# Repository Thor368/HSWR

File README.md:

# HSWR
Fork of the original VESC V6 to support up to 200V and 100A (depending on cooling)

#Work in progress (see http://vedder.se/forums/viewtopic.php?f=16&t=568)

#Gen1
Alpha Prototype on self etched boards. Never worked properly.

#Gen2
Four layer design in industry production quality. First working prototype.

#Gen3
Thicker copper layers for higher current capability. Had issues with current sampling.

#Gen3.1
Never was a board but a mod of Gen3. First prototype with Hall current sensors. Worked very well but needed a proper board.

#Gen4
- changed current sensors to halleffect sensors
- many changes in the IO (including connectors breaking backwards compatibility)
- HSWR can now interface with Tritium motor interface boards
- IO now fully isolated from HV
- fan drive
- changed MOSFET mounting mechanism for higher clamping force and reliablity
- some minimal mechanical changes breaking backwards compatibility to HSWR3 housing

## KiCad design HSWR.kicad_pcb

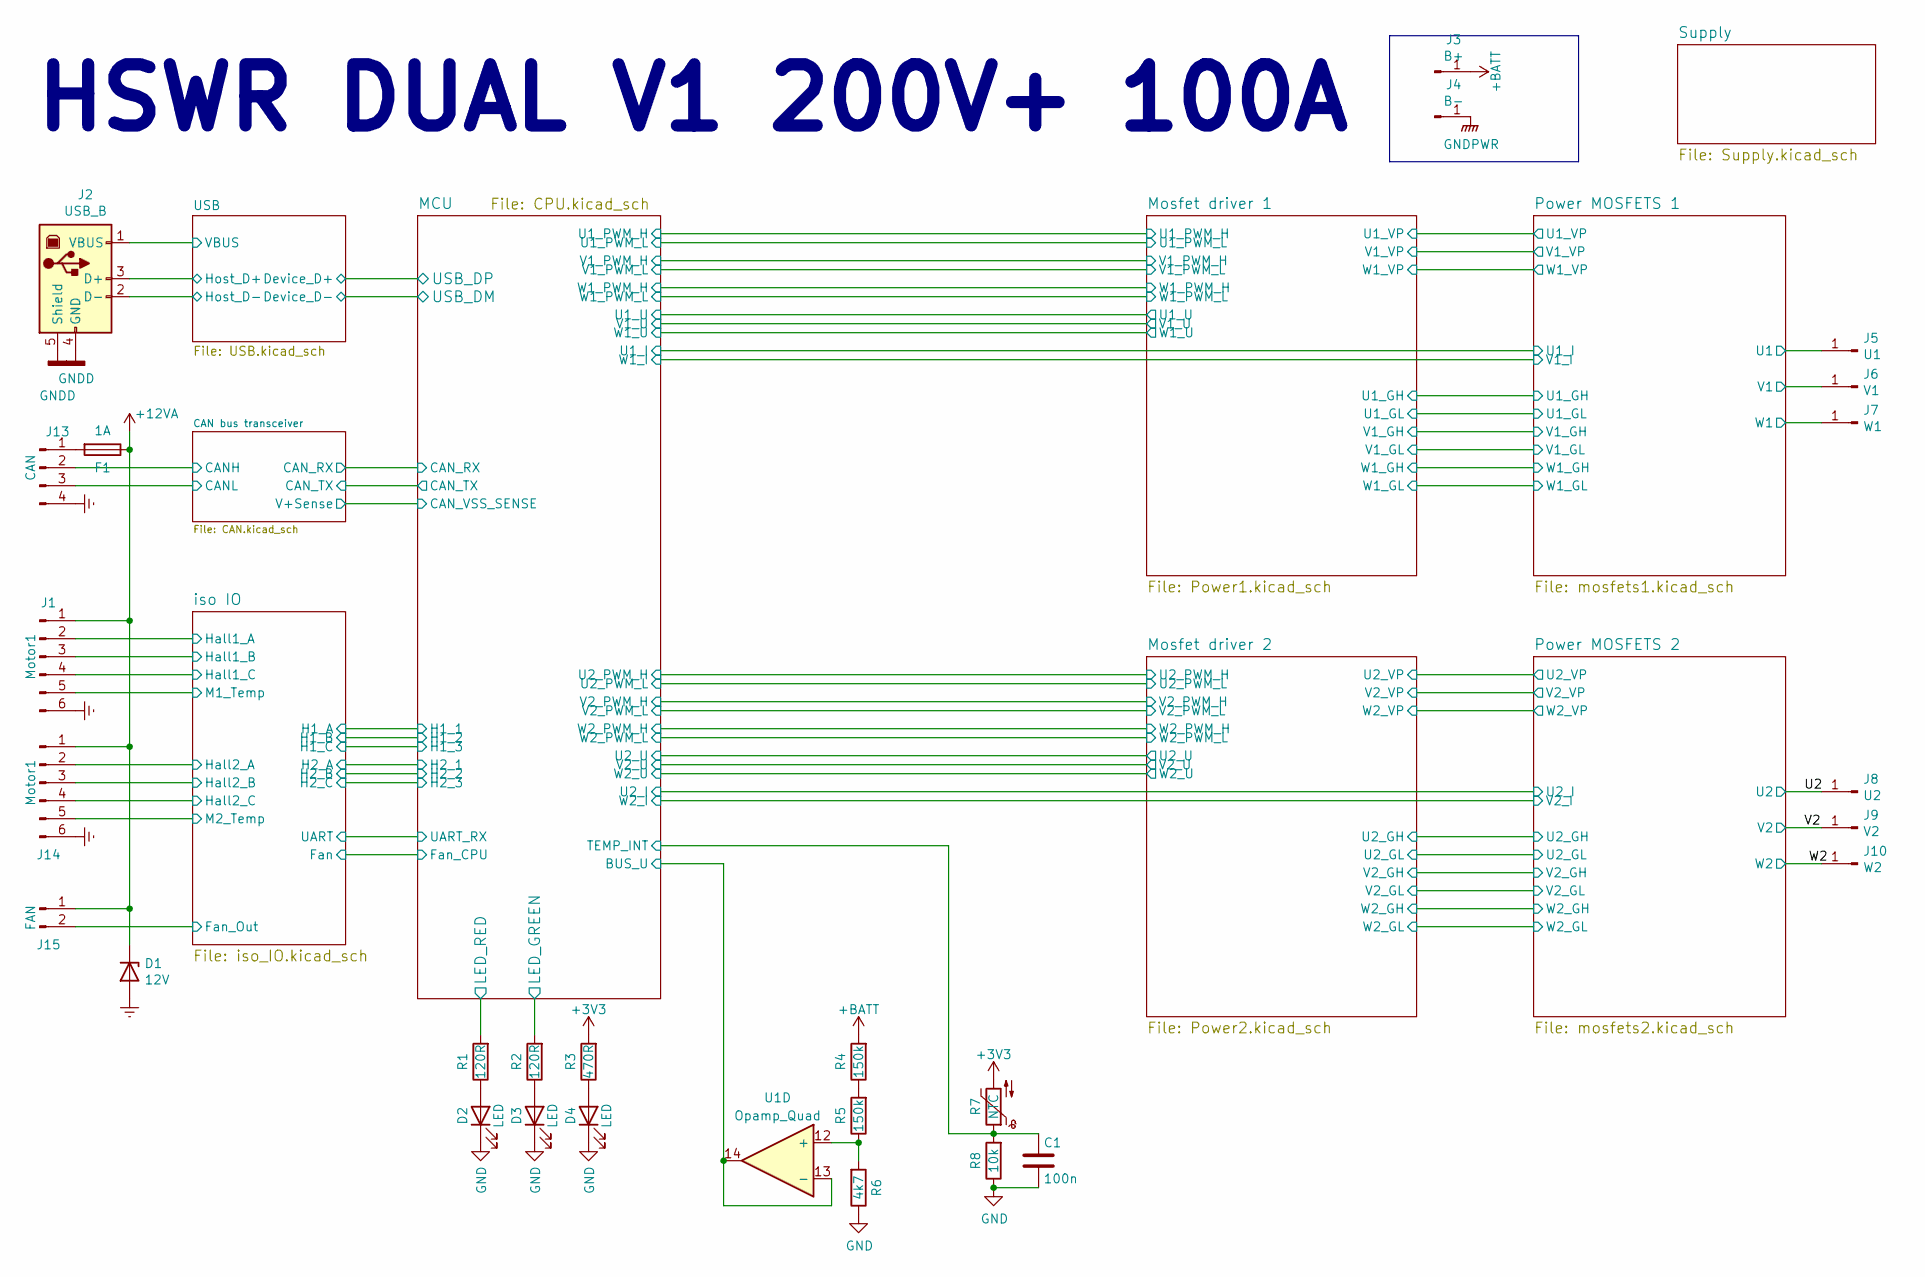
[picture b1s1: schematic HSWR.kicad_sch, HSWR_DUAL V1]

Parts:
C1: 100n; C_0805_2012Metric
D1: 12V; D_SMA
D2, D3, D4: LED; LED_0805_2012Metric
F1: 1A; Fuse_Littelfuse-NANO2-451_453
J1, J14: Motor1; PhoenixContact_MCV_1,5_6-G-3.5_1x06_P3.50mm_Vertical
J2: USB_B; USB_B_TE_5787834_Vertical
J3: B+; MountingHole_6.5mm_Pad_Via
J4: B-; MountingHole_6.5mm_Pad_Via
J5: U1; MountingHole_6.5mm_Pad_Via
J6: V1; MountingHole_6.5mm_Pad_Via
J7: W1; MountingHole_6.5mm_Pad_Via
J8: U2; MountingHole_6.5mm_Pad_Via
J9: V2; MountingHole_6.5mm_Pad_Via
J10: W2; MountingHole_6.5mm_Pad_Via
J13: CAN; PhoenixContact_MCV_1,5_4-G-3.5_1x04_P3.50mm_Vertical
J15: FAN; PhoenixContact_MCV_1,5_2-G-3.5_1x02_P3.50mm_Vertical
R1, R2: 120R; R_0805_2012Metric
R3: 470R; R_0805_2012Metric
R4, R5: 150k; R_0805_2012Metric
R6: 4k7; R_0805_2012Metric
R7: NTC; R_0603_1608Metric
R8: 10k; R_0805_2012Metric
U1: Opamp_Quad; SO-14_3.9x8.65mm_P1.27mm

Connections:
+3V3: R3.2, R7.2; also elsewhere on the board
+12VA: D1.1 (K), F1.1, J1.1, J14.1, J15.1; also elsewhere on the board
+BATT: J3.1, R4.2; also elsewhere on the board
/CAN bus transceiver/CANH: J13.2; also elsewhere on the board
/CAN bus transceiver/CANL: J13.3; also elsewhere on the board
/MCU/BUS_U: U1.13 (-), U1.14; also elsewhere on the board
/MCU/LED_GREEN: R2.2; also elsewhere on the board
/MCU/LED_RED: R1.2; also elsewhere on the board
/MCU/TEMP_INT: C1.1, R7.1, R8.2; also elsewhere on the board
/Mosfet driver 1/W1_VP: J7.1; also elsewhere on the board
/Power MOSFETS 1/U1: J5.1; also elsewhere on the board
/Power MOSFETS 1/V1: J6.1; also elsewhere on the board
/U2: J8.1; also elsewhere on the board
/USB/Host_D+: J2.3 (D+); also elsewhere on the board
/USB/Host_D-: J2.2 (D-); also elsewhere on the board
/USB/VBUS: J2.1 (VBUS); also elsewhere on the board
/V2: J9.1; also elsewhere on the board
/W2: J10.1; also elsewhere on the board
/iso IO/Fan_Out: J15.2; also elsewhere on the board
/iso IO/Hall1_A: J1.2; also elsewhere on the board
/iso IO/Hall1_B: J1.3; also elsewhere on the board
/iso IO/Hall1_C: J1.4; also elsewhere on the board
/iso IO/Hall2_A: J14.2; also elsewhere on the board
/iso IO/Hall2_B: J14.3; also elsewhere on the board
/iso IO/Hall2_C: J14.4; also elsewhere on the board
/iso IO/M1_Temp: J1.5; also elsewhere on the board
/iso IO/M2_Temp: J14.5; also elsewhere on the board
Earth: D1.2 (A), J1.6, J13.4, J14.6; also elsewhere on the board
GND: C1.2, D2.1 (K), D3.1 (K), D4.1 (K), R6.1, R8.1; also elsewhere on the board
GNDD: J2.4 (GND), J2.5 (Shield); also elsewhere on the board
GNDPWR: J4.1; also elsewhere on the board
unnamed: D2.2 (A), R1.1
unnamed: D3.2 (A), R2.1
unnamed: D4.2 (A), R3.1
unnamed: F1.2, J13.1
unnamed: R4.1, R5.2
unnamed: R5.1, R6.2, U1.12 (+)

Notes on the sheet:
HSWR DUAL V1 200V+ 100A

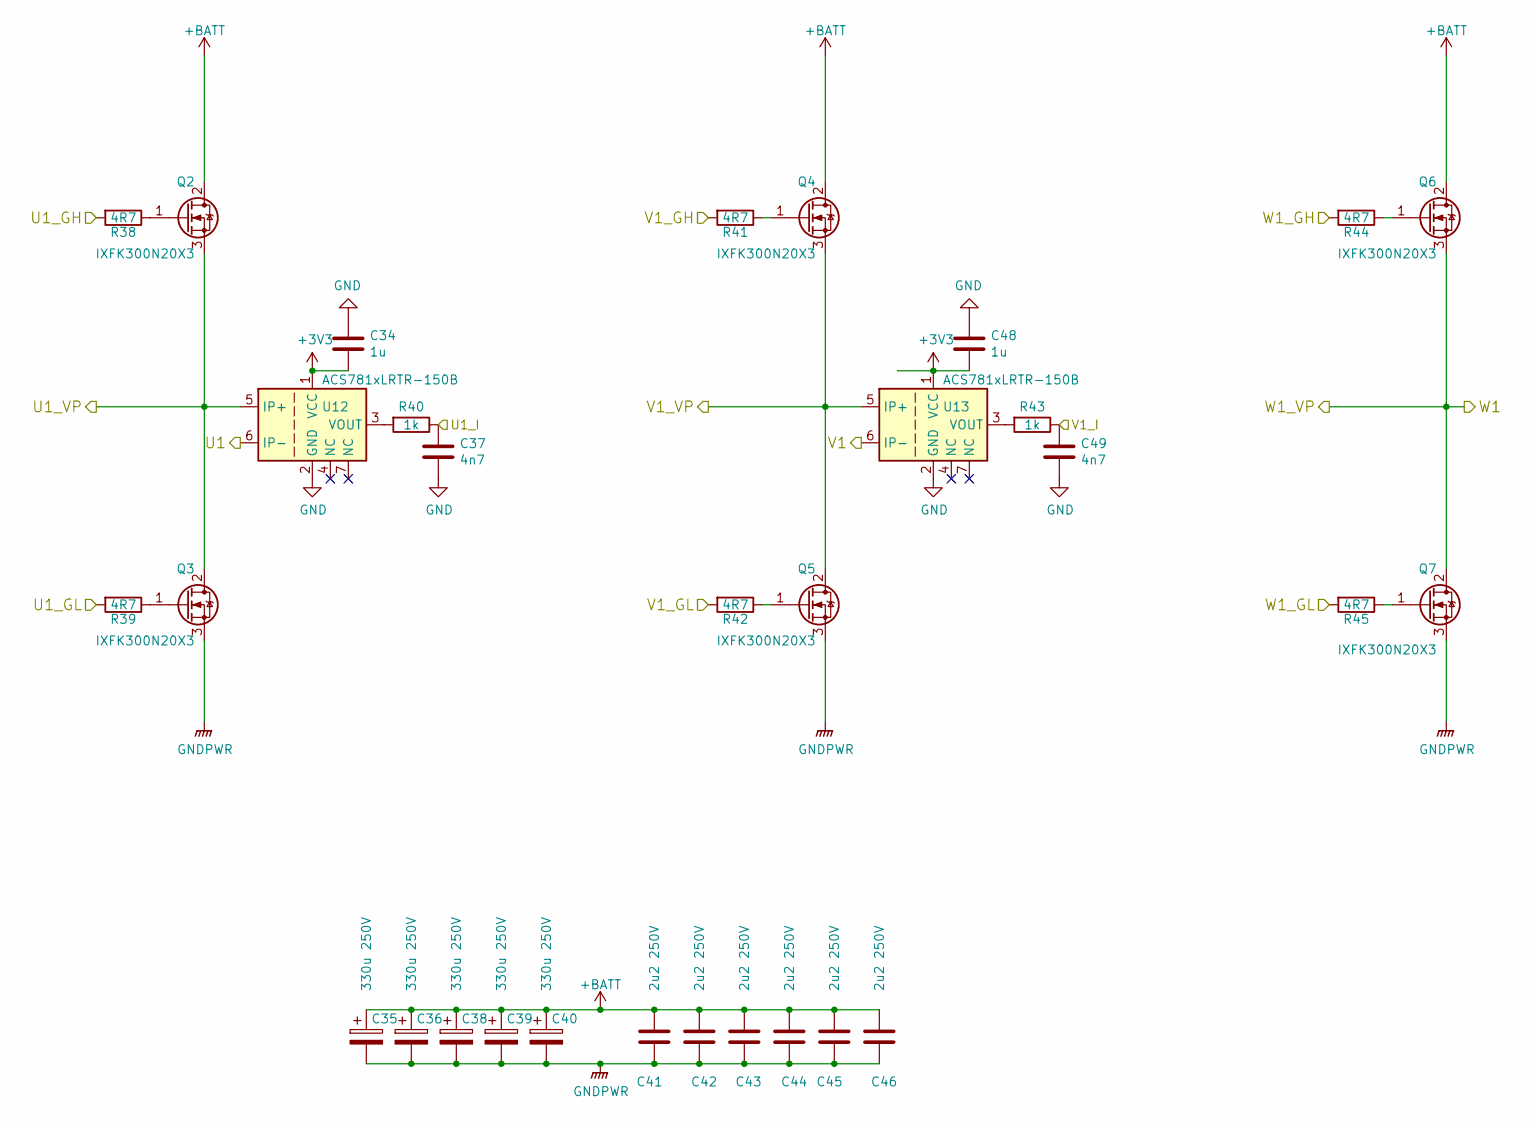
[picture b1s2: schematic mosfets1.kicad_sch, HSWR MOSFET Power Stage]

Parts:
C34, C48: 1u; C_0805_2012Metric
C35, C36, C38, C39, C40: 330u 250V; CP_Radial_D22.0mm_P10.00mm_SnapIn
C37, C49: 4n7; C_0805_2012Metric
C41, C42, C43, C44, C45, C46: 2u2 250V; C_2220_5750Metric
Q2, Q3, Q4, Q5, Q6, Q7: IXFK300N20X3; TO-264-3_Horizontal_TabUp_6mm_hole
R38, R39, R41, R42, R44, R45: 4R7; R_0805_2012Metric
R40, R43: 1k; R_0805_2012Metric
U12, U13: ACS781xLRTR-150B; Allegro_PSOF-7_4.8x6.4mm_P1.60mm

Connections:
+3V3: C34.2, C48.2, U12.1 (VCC), U13.1 (VCC); also elsewhere on the board
+BATT: C35.1, C36.1, C38.1, C39.1, C40.1, C41.1, C42.1, C43.1, C44.1, C45.1, C46.1, Q2.2 (D), Q4.2 (D), Q6.2 (D); also elsewhere on the board
/MCU/U1_I: C37.1, R40.1; also elsewhere on the board
/MCU/W1_I: C49.1, R43.1; also elsewhere on the board
/Mosfet driver 1/U1_GH: R38.2; also elsewhere on the board
/Mosfet driver 1/U1_GL: R39.2; also elsewhere on the board
/Mosfet driver 1/U1_VP: Q2.3 (S), Q3.2 (D), U12.5 (IP+); also elsewhere on the board
/Mosfet driver 1/V1_GH: R41.2; also elsewhere on the board
/Mosfet driver 1/V1_GL: R42.2; also elsewhere on the board
/Mosfet driver 1/V1_VP: Q4.3 (S), Q5.2 (D), U13.5 (IP+); also elsewhere on the board
/Mosfet driver 1/W1_GH: R44.2; also elsewhere on the board
/Mosfet driver 1/W1_GL: R45.2; also elsewhere on the board
/Mosfet driver 1/W1_VP: Q6.3 (S), Q7.2 (D); also elsewhere on the board
/Power MOSFETS 1/U1: U12.6 (IP-); also elsewhere on the board
/Power MOSFETS 1/V1: U13.6 (IP-); also elsewhere on the board
GND: C34.1, C37.2, C48.1, C49.2, U12.2 (GND), U13.2 (GND); also elsewhere on the board
GNDPWR: C35.2, C36.2, C38.2, C39.2, C40.2, C41.2, C42.2, C43.2, C44.2, C45.2, C46.2, Q3.3 (S), Q5.3 (S), Q7.3 (S); also elsewhere on the board
unnamed: Q2.1 (G), R38.1
unnamed: Q3.1 (G), R39.1
unnamed: Q4.1 (G), R41.1
unnamed: Q5.1 (G), R42.1
unnamed: Q6.1 (G), R44.1
unnamed: Q7.1 (G), R45.1
unnamed: R40.2, U12.3 (VOUT)
unnamed: R43.2, U13.3 (VOUT)

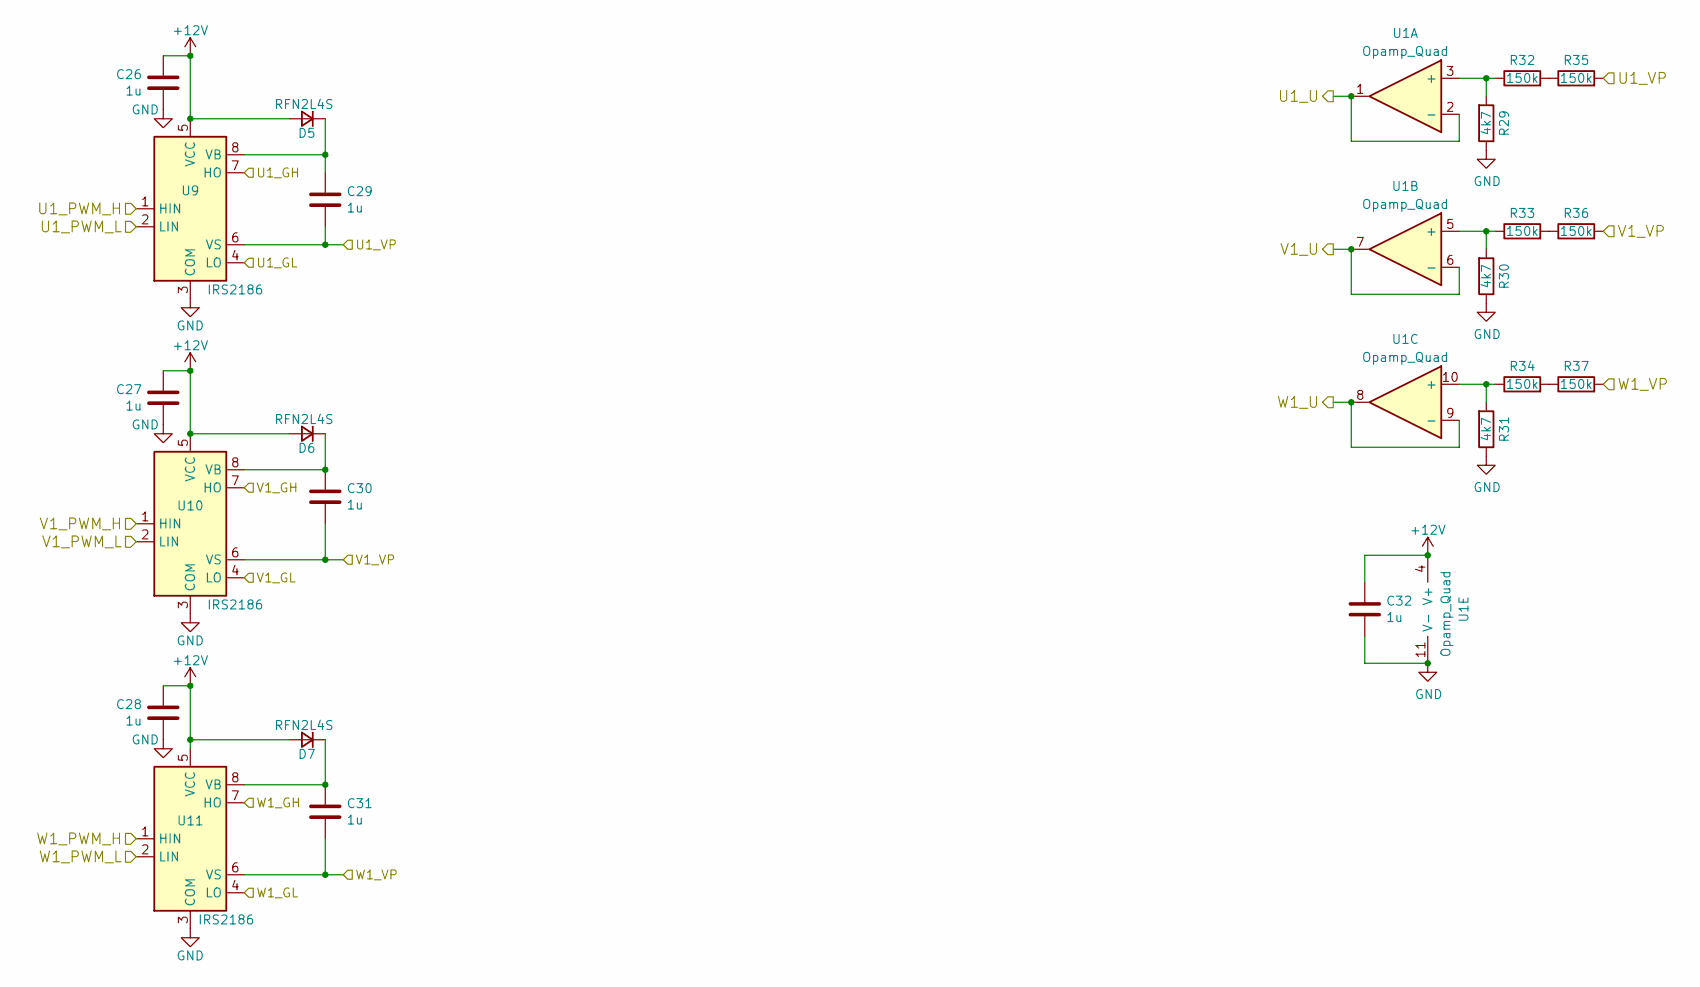
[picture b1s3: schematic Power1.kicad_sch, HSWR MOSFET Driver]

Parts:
C26, C27, C28, C29, C30, C31, C32: 1u; C_0805_2012Metric
D5, D6, D7: RFN2L4S; D_SOD-123
R29, R30, R31: 4k7; R_0805_2012Metric
R32, R33, R34, R35, R36, R37: 150k; R_0805_2012Metric
U1: Opamp_Quad; SO-14_3.9x8.65mm_P1.27mm
U9, U10, U11: IRS2186; SOIC-8_3.9x4.9mm_P1.27mm

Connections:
+12V: C26.2, C27.2, C28.2, C32.1, D5.2 (A), D6.2 (A), D7.2 (A), U1.4 (V+), U9.5 (VCC), U10.5 (VCC), U11.5 (VCC); also elsewhere on the board
/MCU/U1_PWM_H: U9.1 (HIN); also elsewhere on the board
/MCU/U1_PWM_L: U9.2 (LIN); also elsewhere on the board
/MCU/U1_U: U1.1, U1.2 (-); also elsewhere on the board
/MCU/V1_PWM_H: U10.1 (HIN); also elsewhere on the board
/MCU/V1_PWM_L: U10.2 (LIN); also elsewhere on the board
/MCU/V1_U: U1.6 (-), U1.7; also elsewhere on the board
/MCU/W1_PWM_H: U11.1 (HIN); also elsewhere on the board
/MCU/W1_PWM_L: U11.2 (LIN); also elsewhere on the board
/MCU/W1_U: U1.8, U1.9 (-); also elsewhere on the board
/Mosfet driver 1/U1_GH: U9.7 (HO); also elsewhere on the board
/Mosfet driver 1/U1_GL: U9.4 (LO); also elsewhere on the board
/Mosfet driver 1/U1_VP: C29.2, R35.2, U9.6 (VS); also elsewhere on the board
/Mosfet driver 1/V1_GH: U10.7 (HO); also elsewhere on the board
/Mosfet driver 1/V1_GL: U10.4 (LO); also elsewhere on the board
/Mosfet driver 1/V1_VP: C30.2, R36.2, U10.6 (VS); also elsewhere on the board
/Mosfet driver 1/W1_GH: U11.7 (HO); also elsewhere on the board
/Mosfet driver 1/W1_GL: U11.4 (LO); also elsewhere on the board
/Mosfet driver 1/W1_VP: C31.2, R37.2, U11.6 (VS); also elsewhere on the board
GND: C26.1, C27.1, C28.1, C32.2, R29.1, R30.1, R31.1, U1.11 (V-), U9.3 (COM), U10.3 (COM), U11.3 (COM); also elsewhere on the board
unnamed: C29.1, D5.1 (K), U9.8 (VB)
unnamed: C30.1, D6.1 (K), U10.8 (VB)
unnamed: C31.1, D7.1 (K), U11.8 (VB)
unnamed: R32.2, R35.1
unnamed: R33.2, R36.1
unnamed: R34.2, R37.1
unnamed: R29.2, R32.1, U1.3 (+)
unnamed: R30.2, R33.1, U1.5 (+)
unnamed: R31.2, R34.1, U1.10 (+)

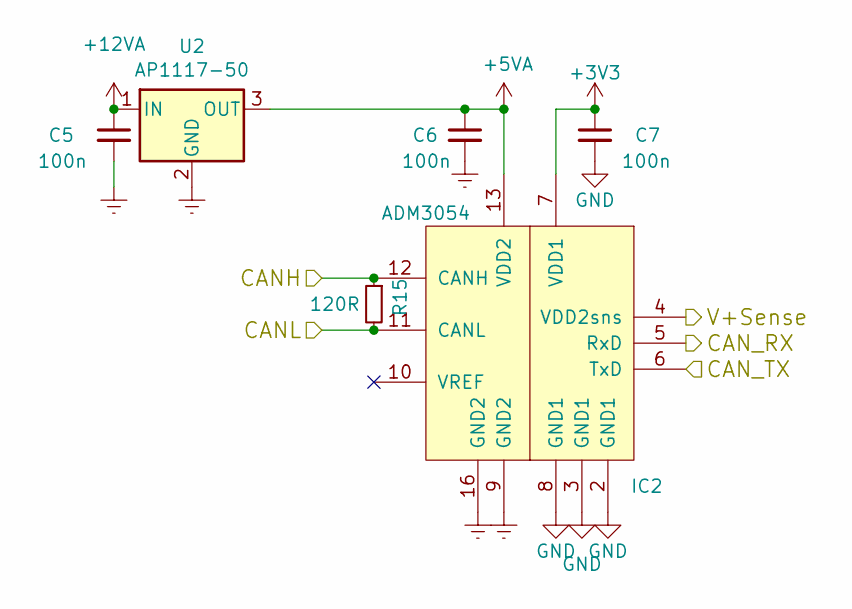
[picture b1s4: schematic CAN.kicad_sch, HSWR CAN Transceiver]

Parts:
C5, C6, C7: 100n; C_0805_2012Metric
IC2: ADM3054; SOIC-16W_7.5x10.3mm_P1.27mm
R15: 120R; R_0805_2012Metric
U2: AP1117-50; SOT-223-3_TabPin2

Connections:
+3V3: C7.1, IC2.7 (VDD1); also elsewhere on the board
+5VA: C6.1, IC2.13 (VDD2), U2.3 (OUT); also elsewhere on the board
+12VA: C5.1, U2.1 (IN); also elsewhere on the board
/CAN bus transceiver/CANH: IC2.12 (CANH), R15.1; also elsewhere on the board
/CAN bus transceiver/CANL: IC2.11 (CANL), R15.2; also elsewhere on the board
/CAN bus transceiver/CAN_RX: IC2.5 (RxD); also elsewhere on the board
/CAN bus transceiver/CAN_TX: IC2.6 (TxD); also elsewhere on the board
/CAN bus transceiver/V+Sense: IC2.4 (VDD2sns); also elsewhere on the board
Earth: C5.2, C6.2, IC2.9 (GND2), IC2.16 (GND2), U2.2 (GND); also elsewhere on the board
GND: C7.2, IC2.2 (GND1), IC2.3 (GND1), IC2.8 (GND1); also elsewhere on the board

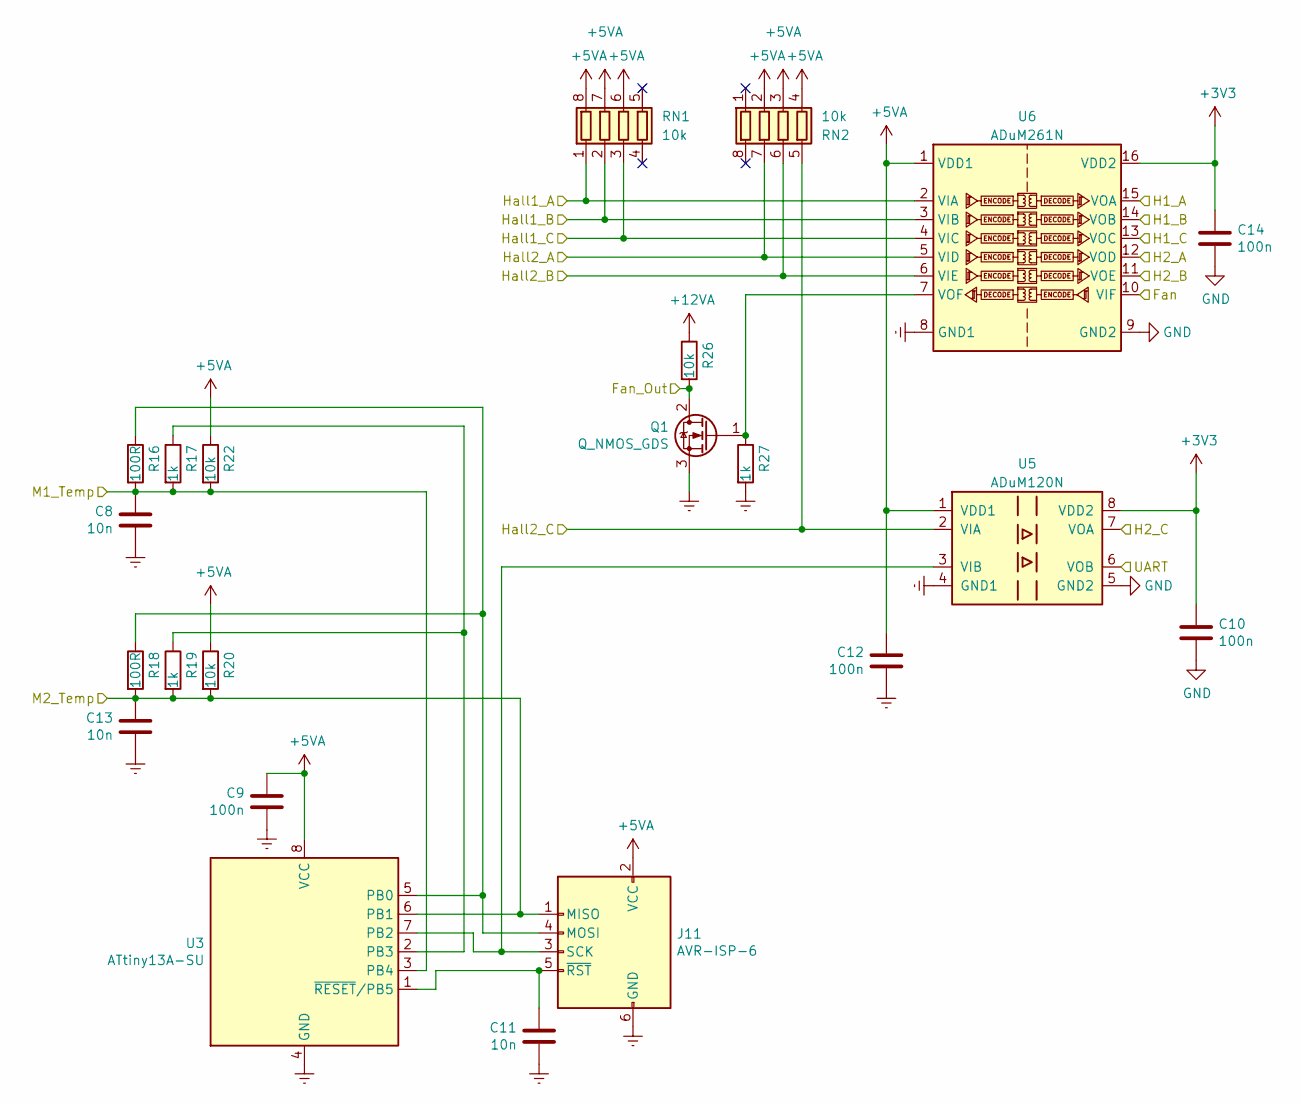
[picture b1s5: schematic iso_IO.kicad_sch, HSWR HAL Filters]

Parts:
C8, C11, C13: 10n; C_0805_2012Metric
C9, C10, C12, C14: 100n; C_0805_2012Metric
J11: AVR-ISP-6; PinHeader_2x03_P2.54mm_Vertical
Q1: Q_NMOS_GDS; SOT-223-3_TabPin2
R16, R18: 100R; R_0805_2012Metric
R17, R19, R27: 1k; R_0805_2012Metric
R20, R22, R26: 10k; R_0805_2012Metric
RN1, RN2: 10k; R_Array_Convex_4x0603
U3: ATtiny13A-SU; SO-8_5.3x6.2mm_P1.27mm
U5: ADuM120N; SOIC-8_3.9x4.9mm_P1.27mm
U6: ADuM261N; SOIC-16W_7.5x12.8mm_P1.27mm

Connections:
+3V3: C10.1, C14.1, U5.8 (VDD2), U6.16 (VDD2); also elsewhere on the board
+5VA: C9.1, C12.1, J11.2 (VCC), R20.1, R22.1, RN1.6 (R3.2), RN1.7 (R2.2), RN1.8 (R1.2), RN2.2 (R2.1), RN2.3 (R3.1), RN2.4 (R4.1), U3.8 (VCC), U5.1 (VDD1), U6.1 (VDD1); also elsewhere on the board
+12VA: R26.1; also elsewhere on the board
/MCU/Fan_CPU: U6.10 (VIF); also elsewhere on the board
/MCU/H1_1: U6.15 (VOA); also elsewhere on the board
/MCU/H1_2: U6.14 (VOB); also elsewhere on the board
/MCU/H1_3: U6.13 (VOC); also elsewhere on the board
/MCU/H2_1: U6.12 (VOD); also elsewhere on the board
/MCU/H2_2: U6.11 (VOE); also elsewhere on the board
/MCU/H2_3: U5.7 (VOA); also elsewhere on the board
/MCU/UART_RX: U5.6 (VOB); also elsewhere on the board
/iso IO/Fan_Out: Q1.2 (D), R26.2; also elsewhere on the board
/iso IO/Hall1_A: RN1.1 (R1.1), U6.2 (VIA); also elsewhere on the board
/iso IO/Hall1_B: RN1.2 (R2.1), U6.3 (VIB); also elsewhere on the board
/iso IO/Hall1_C: RN1.3 (R3.1), U6.4 (VIC); also elsewhere on the board
/iso IO/Hall2_A: RN2.7 (R2.2), U6.5 (VID); also elsewhere on the board
/iso IO/Hall2_B: RN2.6 (R3.2), U6.6 (VIE); also elsewhere on the board
/iso IO/Hall2_C: RN2.5 (R4.2), U5.2 (VIA); also elsewhere on the board
/iso IO/M1_Temp: C8.1, R16.2, R17.2, R22.2, U3.3 (PB4); also elsewhere on the board
/iso IO/M2_Temp: C13.1, J11.1 (MISO), R18.2, R19.2, R20.2, U3.6 (PB1); also elsewhere on the board
Earth: C8.2, C9.2, C11.2, C12.2, C13.2, J11.6 (GND), Q1.3 (S), R27.2, U3.4 (GND), U5.4 (GND1), U6.8 (GND1); also elsewhere on the board
GND: C10.2, C14.2, U5.5 (GND2), U6.9 (GND2); also elsewhere on the board
unnamed: J11.4 (MOSI), R16.1, R18.1, U3.5 (PB0)
unnamed: J11.3 (SCK), U3.7 (PB2), U5.3 (VIB)
unnamed: C11.1, J11.5 (~RST), U3.1 (~RESET/PB5)
unnamed: Q1.1 (G), R27.1, U6.7 (VOF)
unnamed: R17.1, R19.1, U3.2 (PB3)

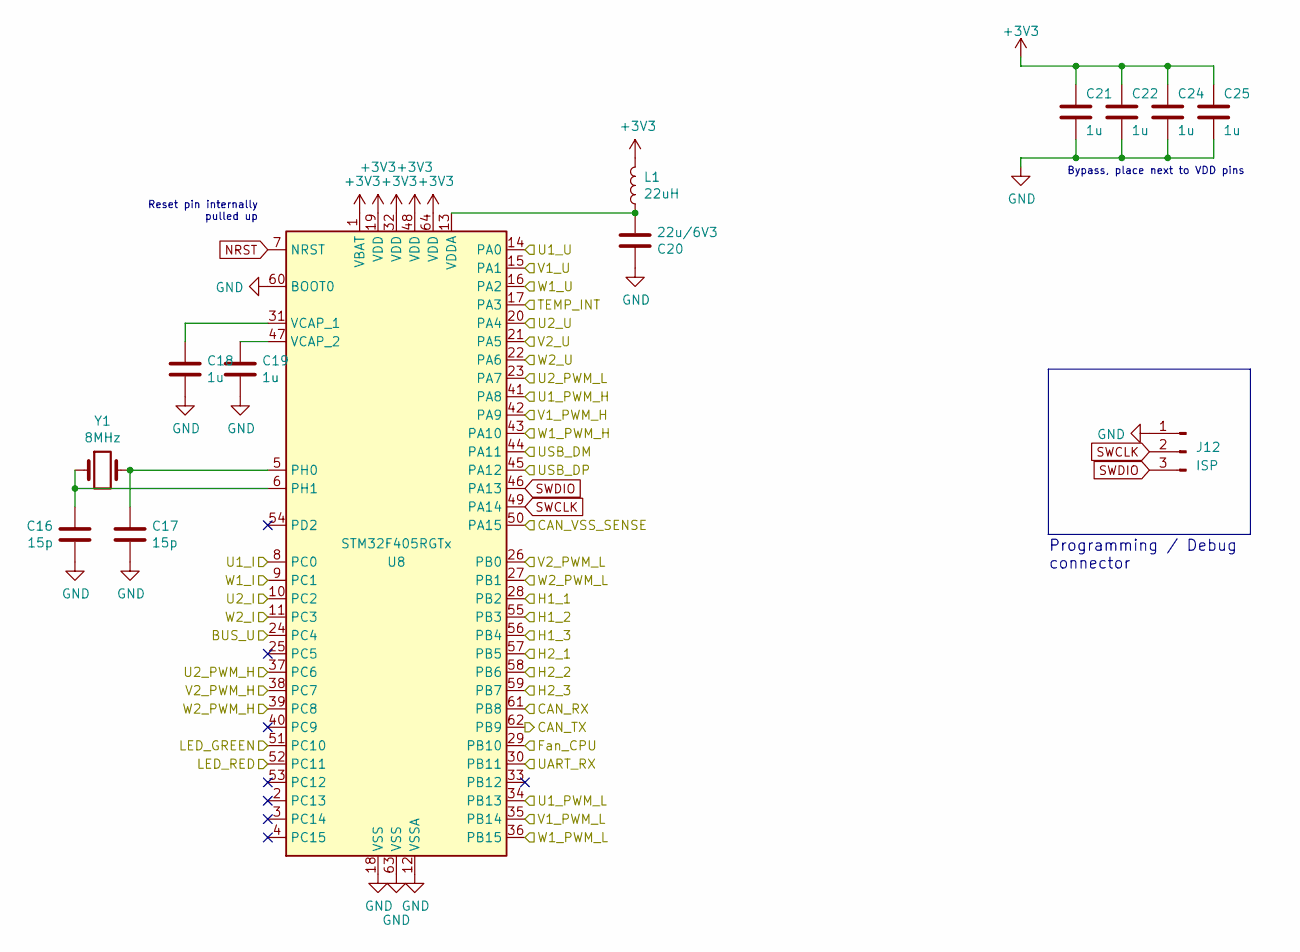
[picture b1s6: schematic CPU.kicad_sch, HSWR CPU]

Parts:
C16, C17: 15p; C_0805_2012Metric
C18, C19, C21, C22, C24, C25: 1u; C_0805_2012Metric
C20: 22u/6V3; C_0805_2012Metric
J12: ISP; PinHeader_1x03_P2.54mm_Vertical
L1: 22uH; L_0805_2012Metric
U8: STM32F405RGTx; LQFP-64_10x10mm_P0.5mm
Y1: 8MHz; Crystal_HC49-4H_Vertical

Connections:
+3V3: C21.1, C22.1, C24.1, C25.1, L1.2, U8.1 (VBAT), U8.19 (VDD), U8.32 (VDD), U8.48 (VDD), U8.64 (VDD); also elsewhere on the board
/CAN bus transceiver/CAN_RX: U8.61 (PB8); also elsewhere on the board
/CAN bus transceiver/CAN_TX: U8.62 (PB9); also elsewhere on the board
/CAN bus transceiver/V+Sense: U8.50 (PA15); also elsewhere on the board
/MCU/BUS_U: U8.24 (PC4); also elsewhere on the board
/MCU/Fan_CPU: U8.29 (PB10); also elsewhere on the board
/MCU/H1_1: U8.28 (PB2); also elsewhere on the board
/MCU/H1_2: U8.55 (PB3); also elsewhere on the board
/MCU/H1_3: U8.56 (PB4); also elsewhere on the board
/MCU/H2_1: U8.57 (PB5); also elsewhere on the board
/MCU/H2_2: U8.58 (PB6); also elsewhere on the board
/MCU/H2_3: U8.59 (PB7); also elsewhere on the board
/MCU/LED_GREEN: U8.51 (PC10); also elsewhere on the board
/MCU/LED_RED: U8.52 (PC11); also elsewhere on the board
/MCU/TEMP_INT: U8.17 (PA3); also elsewhere on the board
/MCU/U1_I: U8.8 (PC0); also elsewhere on the board
/MCU/U1_PWM_H: U8.41 (PA8); also elsewhere on the board
/MCU/U1_PWM_L: U8.34 (PB13); also elsewhere on the board
/MCU/U1_U: U8.14 (PA0); also elsewhere on the board
/MCU/U2_I: U8.10 (PC2); also elsewhere on the board
/MCU/U2_PWM_H: U8.37 (PC6); also elsewhere on the board
/MCU/U2_PWM_L: U8.23 (PA7); also elsewhere on the board
/MCU/U2_U: U8.20 (PA4); also elsewhere on the board
/MCU/UART_RX: U8.30 (PB11); also elsewhere on the board
/MCU/USB_DM: U8.44 (PA11); also elsewhere on the board
/MCU/USB_DP: U8.45 (PA12); also elsewhere on the board
/MCU/V1_PWM_H: U8.42 (PA9); also elsewhere on the board
/MCU/V1_PWM_L: U8.35 (PB14); also elsewhere on the board
/MCU/V1_U: U8.15 (PA1); also elsewhere on the board
/MCU/V2_PWM_H: U8.38 (PC7); also elsewhere on the board
/MCU/V2_PWM_L: U8.26 (PB0); also elsewhere on the board
/MCU/V2_U: U8.21 (PA5); also elsewhere on the board
/MCU/W1_I: U8.9 (PC1); also elsewhere on the board
/MCU/W1_PWM_H: U8.43 (PA10); also elsewhere on the board
/MCU/W1_PWM_L: U8.36 (PB15); also elsewhere on the board
/MCU/W1_U: U8.16 (PA2); also elsewhere on the board
/MCU/W2_I: U8.11 (PC3); also elsewhere on the board
/MCU/W2_PWM_H: U8.39 (PC8); also elsewhere on the board
/MCU/W2_PWM_L: U8.27 (PB1); also elsewhere on the board
/MCU/W2_U: U8.22 (PA6); also elsewhere on the board
GND: C16.1, C17.2, C18.2, C19.2, C20.1, C21.2, C22.2, C24.2, C25.2, J12.1, U8.12 (VSSA), U8.18 (VSS), U8.60 (BOOT0), U8.63 (VSS); also elsewhere on the board
NRST: U8.7 (NRST)
unnamed: C17.1, U8.5 (PH0), Y1.2
unnamed: C16.2, U8.6 (PH1), Y1.1
unnamed: C18.1, U8.31 (VCAP_1)
unnamed: C19.1, U8.47 (VCAP_2)
unnamed: C20.2, L1.1, U8.13 (VDDA)
SWCLK: J12.2, U8.49 (PA14)
SWDIO: J12.3, U8.46 (PA13)

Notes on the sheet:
Reset pin internally pulled up
Bypass, place next to VDD pins
Programming / Debug connector

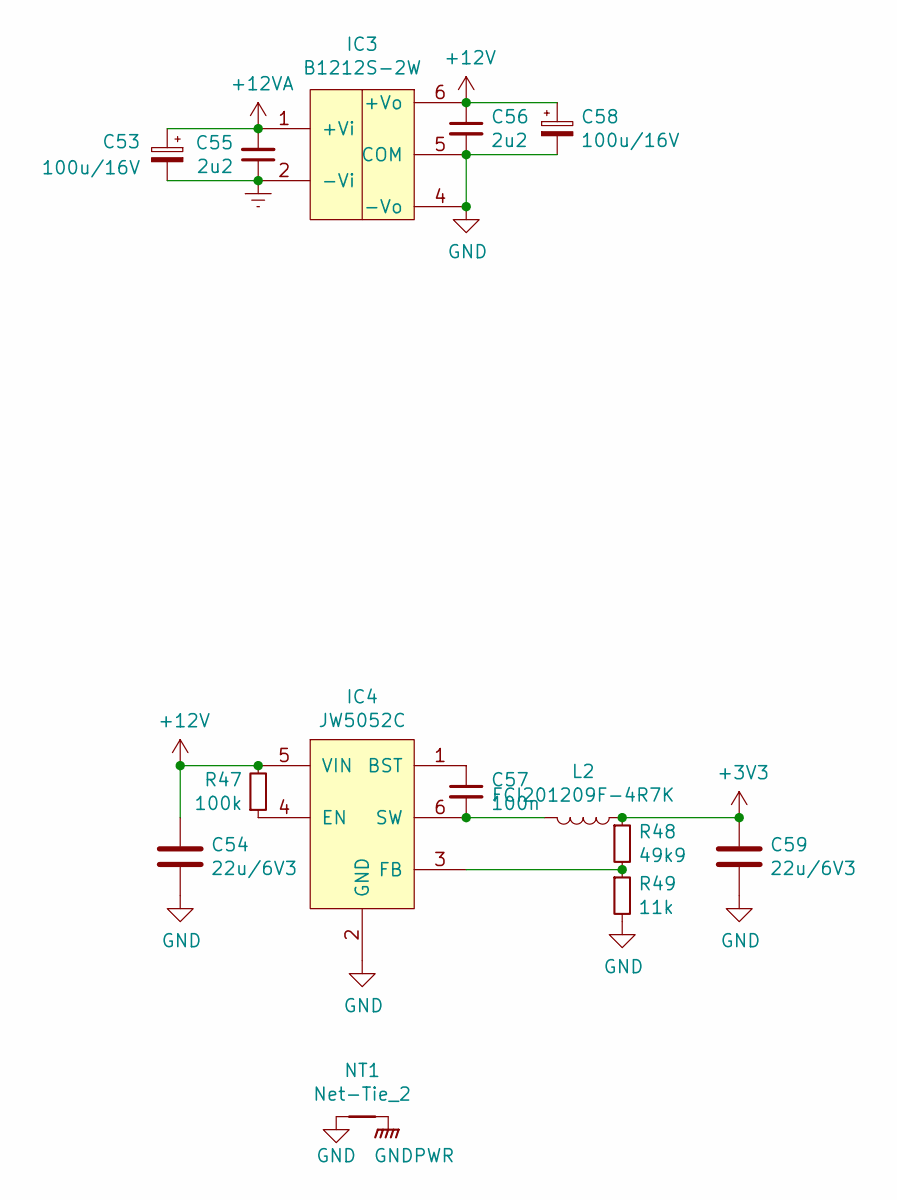
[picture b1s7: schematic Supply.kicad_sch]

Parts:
C53, C58: 100u/16V; CP_Radial_D6.3mm_P2.50mm
C54, C59: 22u/6V3; C_0805_2012Metric
C55, C56: 2u2; C_0805_2012Metric
C57: 100n; C_0805_2012Metric
IC3: B1212S-2W; Converter_DCDC_muRata_NMAxxxxSC_THT
IC4: JW5052C; TSOT-23-6
L2: FCI201209F-4R7K; L_0805_2012Metric
NT1: Net-Tie_2; NetTie-2_SMD_Pad2.0mm
R47: 100k; R_0805_2012Metric
R48: 49k9; R_0805_2012Metric
R49: 11k; R_0805_2012Metric

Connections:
+3V3: C59.1, L2.1, R48.1; also elsewhere on the board
+12V: C54.1, C56.1, C58.1, IC3.6 (+Vo), IC4.5 (VIN), R47.2; also elsewhere on the board
+12VA: C53.1, C55.2, IC3.1 (+Vi); also elsewhere on the board
Earth: C53.2, C55.1, IC3.2 (-Vi); also elsewhere on the board
GND: C54.2, C56.2, C58.2, C59.2, IC3.4 (-Vo), IC3.5 (COM), IC4.2 (GND), NT1.1, R49.2; also elsewhere on the board
GNDPWR: NT1.2; also elsewhere on the board
unnamed: C57.1, IC4.1 (BST)
unnamed: IC4.4 (EN), R47.1
unnamed: IC4.3 (FB), R48.2, R49.1
unnamed: C57.2, IC4.6 (SW), L2.2

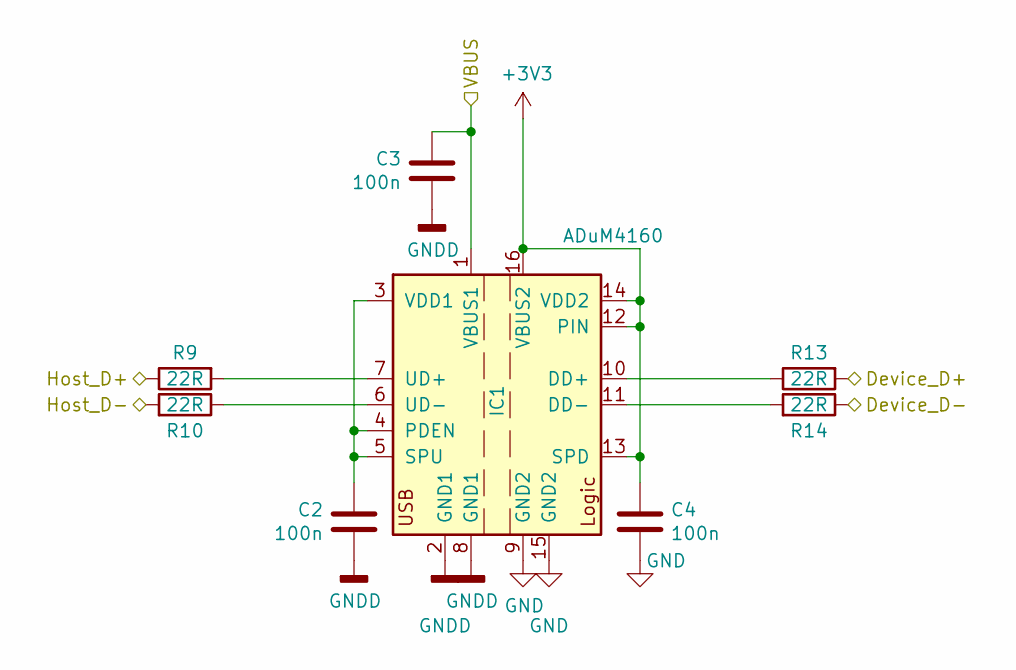
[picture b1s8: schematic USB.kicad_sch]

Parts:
C2, C3, C4: 100n; C_0805_2012Metric
IC1: ADuM4160; SOIC-16W_7.5x10.3mm_P1.27mm
R9, R10, R13, R14: 22R; R_0805_2012Metric

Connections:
+3V3: C4.2, IC1.12 (PIN), IC1.13 (SPD), IC1.14 (VDD2), IC1.16 (VBUS2); also elsewhere on the board
/MCU/USB_DM: R14.1; also elsewhere on the board
/MCU/USB_DP: R13.2; also elsewhere on the board
/USB/Host_D+: R9.1; also elsewhere on the board
/USB/Host_D-: R10.2; also elsewhere on the board
/USB/VBUS: C3.2, IC1.1 (VBUS1); also elsewhere on the board
GND: C4.1, IC1.9 (GND2), IC1.15 (GND2); also elsewhere on the board
GNDD: C2.1, C3.1, IC1.2 (GND1), IC1.8 (GND1); also elsewhere on the board
unnamed: IC1.10 (DD+), R13.1
unnamed: IC1.11 (DD-), R14.2
unnamed: C2.2, IC1.3 (VDD1), IC1.4 (PDEN), IC1.5 (SPU)
unnamed: IC1.7 (UD+), R9.2
unnamed: IC1.6 (UD-), R10.1

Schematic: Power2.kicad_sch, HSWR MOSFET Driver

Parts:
C60, C61, C62, C63, C64, C65: 1u; C_0805_2012Metric
D8, D9, D10: RFN2L4S; D_SOD-123
R50, R51, R52: 4k7; R_0805_2012Metric
R53, R54, R55, R56, R57, R58: 150k; R_0805_2012Metric
U15, U16, U17: IRS2186; SOIC-8_3.9x4.9mm_P1.27mm
U18: Opamp_Quad; SO-14_3.9x8.65mm_P1.27mm

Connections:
+12V: C60.2, C61.2, C62.2, D8.2 (A), D9.2 (A), D10.2 (A), U15.5 (VCC), U16.5 (VCC), U17.5 (VCC), U18.4 (V+); also elsewhere on the board
/MCU/U2_PWM_H: U15.1 (HIN); also elsewhere on the board
/MCU/U2_PWM_L: U15.2 (LIN); also elsewhere on the board
/MCU/U2_U: U18.1, U18.2 (-); also elsewhere on the board
/MCU/V2_PWM_H: U16.1 (HIN); also elsewhere on the board
/MCU/V2_PWM_L: U16.2 (LIN); also elsewhere on the board
/MCU/V2_U: U18.6 (-), U18.7; also elsewhere on the board
/MCU/W2_PWM_H: U17.1 (HIN); also elsewhere on the board
/MCU/W2_PWM_L: U17.2 (LIN); also elsewhere on the board
/MCU/W2_U: U18.8, U18.9 (-); also elsewhere on the board
/Mosfet driver 2/U2_GH: U15.7 (HO); also elsewhere on the board
/Mosfet driver 2/U2_GL: U15.4 (LO); also elsewhere on the board
/Mosfet driver 2/U2_VP: C63.2, R56.2, U15.6 (VS); also elsewhere on the board
/Mosfet driver 2/V2_GH: U16.7 (HO); also elsewhere on the board
/Mosfet driver 2/V2_GL: U16.4 (LO); also elsewhere on the board
/Mosfet driver 2/V2_VP: C64.2, R57.2, U16.6 (VS); also elsewhere on the board
/Mosfet driver 2/W2_GH: U17.7 (HO); also elsewhere on the board
/Mosfet driver 2/W2_GL: U17.4 (LO); also elsewhere on the board
/W2: C65.2, R58.2, U17.6 (VS); also elsewhere on the board
GND: C60.1, C61.1, C62.1, R50.1, R51.1, R52.1, U15.3 (COM), U16.3 (COM), U17.3 (COM), U18.11 (V-), U18.12 (+); also elsewhere on the board
unnamed: C63.1, D8.1 (K), U15.8 (VB)
unnamed: C64.1, D9.1 (K), U16.8 (VB)
unnamed: C65.1, D10.1 (K), U17.8 (VB)
unnamed: R53.2, R56.1
unnamed: R54.2, R57.1
unnamed: R55.2, R58.1
unnamed: R50.2, R53.1, U18.3 (+)
unnamed: R51.2, R54.1, U18.5 (+)
unnamed: R52.2, R55.1, U18.10 (+)
unnamed: U18.13 (-), U18.14

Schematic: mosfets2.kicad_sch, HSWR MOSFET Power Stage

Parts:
C68, C82: 1u; C_0805_2012Metric
C69, C70, C72, C73, C74: 330u 250V; CP_Radial_D22.0mm_P10.00mm_SnapIn
C71, C83: 4n7; C_0805_2012Metric
C75, C76, C77, C78, C79, C80: 2u2 250V; C_2220_5750Metric
Q8, Q9, Q10, Q11, Q12, Q13: IXFK300N20X3; TO-264-3_Horizontal_TabUp_6mm_hole
R59, R60, R62, R63, R65, R66: 4R7; R_0805_2012Metric
R61, R64: 1k; R_0805_2012Metric
U19, U20: ACS781xLRTR-150B; Allegro_PSOF-7_4.8x6.4mm_P1.60mm

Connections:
+3V3: C68.2, C82.2, U19.1 (VCC), U20.1 (VCC); also elsewhere on the board
+BATT: C69.1, C70.1, C72.1, C73.1, C74.1, C75.1, C76.1, C77.1, C78.1, C79.1, C80.1, Q8.2 (D), Q10.2 (D), Q12.2 (D); also elsewhere on the board
/MCU/U2_I: C71.1, R61.1; also elsewhere on the board
/MCU/W2_I: C83.1, R64.1; also elsewhere on the board
/Mosfet driver 2/U2_GH: R59.2; also elsewhere on the board
/Mosfet driver 2/U2_GL: R60.2; also elsewhere on the board
/Mosfet driver 2/U2_VP: Q8.3 (S), Q9.2 (D), U19.5 (IP+); also elsewhere on the board
/Mosfet driver 2/V2_GH: R62.2; also elsewhere on the board
/Mosfet driver 2/V2_GL: R63.2; also elsewhere on the board
/Mosfet driver 2/V2_VP: Q10.3 (S), Q11.2 (D), U20.5 (IP+); also elsewhere on the board
/Mosfet driver 2/W2_GH: R65.2; also elsewhere on the board
/Mosfet driver 2/W2_GL: R66.2; also elsewhere on the board
/U2: U19.6 (IP-); also elsewhere on the board
/V2: U20.6 (IP-); also elsewhere on the board
/W2: Q12.3 (S), Q13.2 (D); also elsewhere on the board
GND: C68.1, C71.2, C82.1, C83.2, U19.2 (GND), U20.2 (GND); also elsewhere on the board
GNDPWR: C69.2, C70.2, C72.2, C73.2, C74.2, C75.2, C76.2, C77.2, C78.2, C79.2, C80.2, Q9.3 (S), Q11.3 (S), Q13.3 (S); also elsewhere on the board
unnamed: Q8.1 (G), R59.1
unnamed: Q9.1 (G), R60.1
unnamed: Q10.1 (G), R62.1
unnamed: Q11.1 (G), R63.1
unnamed: Q12.1 (G), R65.1
unnamed: Q13.1 (G), R66.1
unnamed: R61.2, U19.3 (VOUT)
unnamed: R64.2, U20.3 (VOUT)
